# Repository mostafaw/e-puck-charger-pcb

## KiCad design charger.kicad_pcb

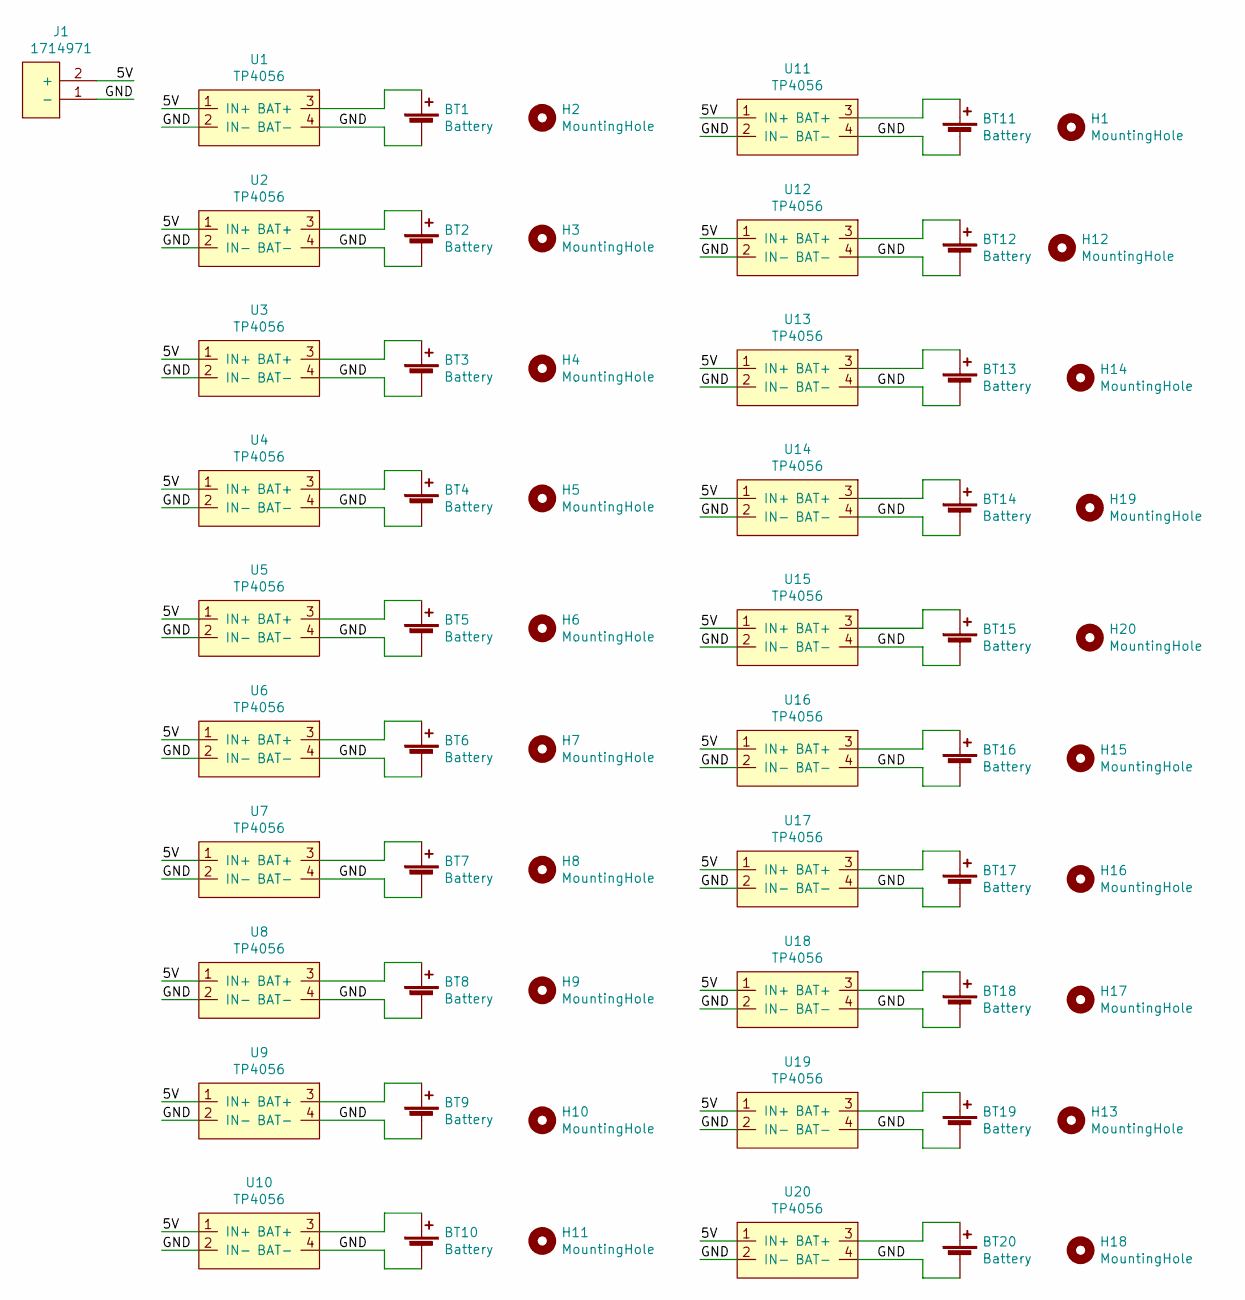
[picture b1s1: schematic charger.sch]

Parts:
BT1, BT2, BT3, BT4, BT5, BT6, BT7, BT8, BT9, BT10, BT11, BT12, BT13, BT14, BT15, BT16, BT17, BT18, BT19, BT20: Battery; Battery_holder
H1, H2, H3, H4, H5, H6, H7, H8, H9, H10, H11, H12, H13, H14, H15, H16, H17, H18, H19, H20: MountingHole; MountingHole_2.7mm_M2.5
J1: 1714971; Terminal_block
U1, U2, U3, U4, U5, U6, U7, U8, U9, U10, U11, U12, U13, U14, U15, U16, U17, U18, U19, U20: TP4056

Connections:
/5V: J1.2 (+), U1.1 (IN+), U2.1 (IN+), U3.1 (IN+), U4.1 (IN+), U5.1 (IN+), U6.1 (IN+), U7.1 (IN+), U8.1 (IN+), U9.1 (IN+), U10.1 (IN+), U11.1 (IN+), U12.1 (IN+), U13.1 (IN+), U14.1 (IN+), U15.1 (IN+), U16.1 (IN+), U17.1 (IN+), U18.1 (IN+), U19.1 (IN+), U20.1 (IN+)
/GND: BT1.2 (-), BT2.2 (-), BT3.2 (-), BT4.2 (-), BT5.2 (-), BT6.2 (-), BT7.2 (-), BT8.2 (-), BT9.2 (-), BT10.2 (-), BT11.2 (-), BT12.2 (-), BT13.2 (-), BT14.2 (-), BT15.2 (-), BT16.2 (-), BT17.2 (-), BT18.2 (-), BT19.2 (-), BT20.2 (-), J1.1 (-), U1.2 (IN-), U1.4 (BAT-), U2.2 (IN-), U2.4 (BAT-), U3.2 (IN-), U3.4 (BAT-), U4.2 (IN-), U4.4 (BAT-), U5.2 (IN-), U5.4 (BAT-), U6.2 (IN-), U6.4 (BAT-), U7.2 (IN-), U7.4 (BAT-), U8.2 (IN-), U8.4 (BAT-), U9.2 (IN-), U9.4 (BAT-), U10.2 (IN-), U10.4 (BAT-), U11.2 (IN-), U11.4 (BAT-), U12.2 (IN-), U12.4 (BAT-), U13.2 (IN-), U13.4 (BAT-), U14.2 (IN-), U14.4 (BAT-), U15.2 (IN-), U15.4 (BAT-), U16.2 (IN-), U16.4 (BAT-), U17.2 (IN-), U17.4 (BAT-), U18.2 (IN-), U18.4 (BAT-), U19.2 (IN-), U19.4 (BAT-), U20.2 (IN-), U20.4 (BAT-)
unnamed: BT1.1 (+), U1.3 (BAT+)
unnamed: BT2.1 (+), U2.3 (BAT+)
unnamed: BT3.1 (+), U3.3 (BAT+)
unnamed: BT4.1 (+), U4.3 (BAT+)
unnamed: BT5.1 (+), U5.3 (BAT+)
unnamed: BT6.1 (+), U6.3 (BAT+)
unnamed: BT7.1 (+), U7.3 (BAT+)
unnamed: BT8.1 (+), U8.3 (BAT+)
unnamed: BT9.1 (+), U9.3 (BAT+)
unnamed: BT10.1 (+), U10.3 (BAT+)
unnamed: BT11.1 (+), U11.3 (BAT+)
unnamed: BT12.1 (+), U12.3 (BAT+)
unnamed: BT13.1 (+), U13.3 (BAT+)
unnamed: BT14.1 (+), U14.3 (BAT+)
unnamed: BT15.1 (+), U15.3 (BAT+)
unnamed: BT16.1 (+), U16.3 (BAT+)
unnamed: BT17.1 (+), U17.3 (BAT+)
unnamed: BT18.1 (+), U18.3 (BAT+)
unnamed: BT19.1 (+), U19.3 (BAT+)
unnamed: BT20.1 (+), U20.3 (BAT+)

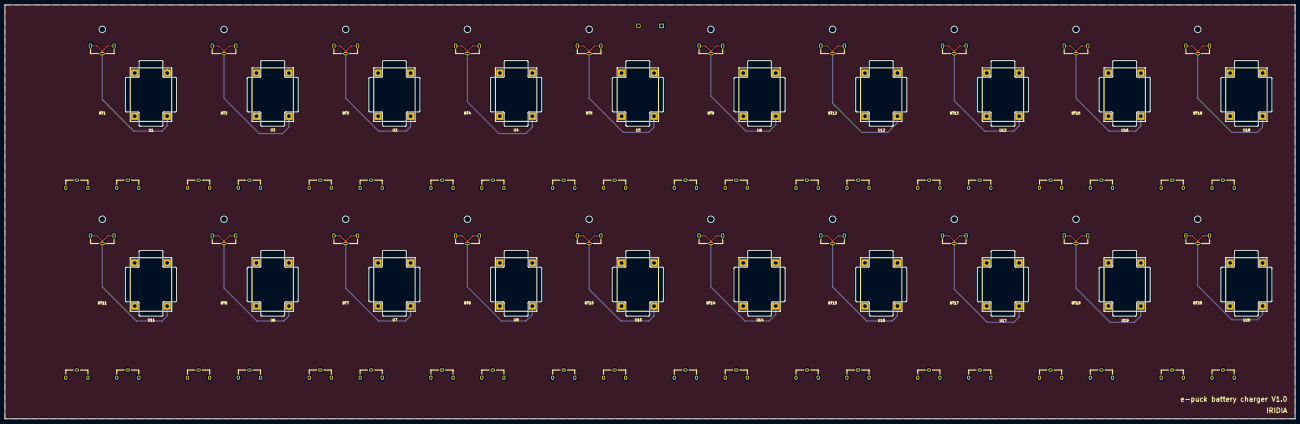
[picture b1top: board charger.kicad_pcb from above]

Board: 2 copper layers, 530.0 x 170.0 mm, 61 parts (1 on the bottom side), 22 nets.

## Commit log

2020-02-21 added new project
2020-02-21 added TP4056 footprint and model
2020-02-21 git ignore
2020-02-21 test
2020-02-21 testing github/slack integration
2020-03-10 added battery holder footprint and 3d models
2020-03-11 finishing up the schematic
2020-03-13 routing completed
2020-03-16 added mounting holes
2020-03-21 added filed zones
2020-03-21 minor changes
